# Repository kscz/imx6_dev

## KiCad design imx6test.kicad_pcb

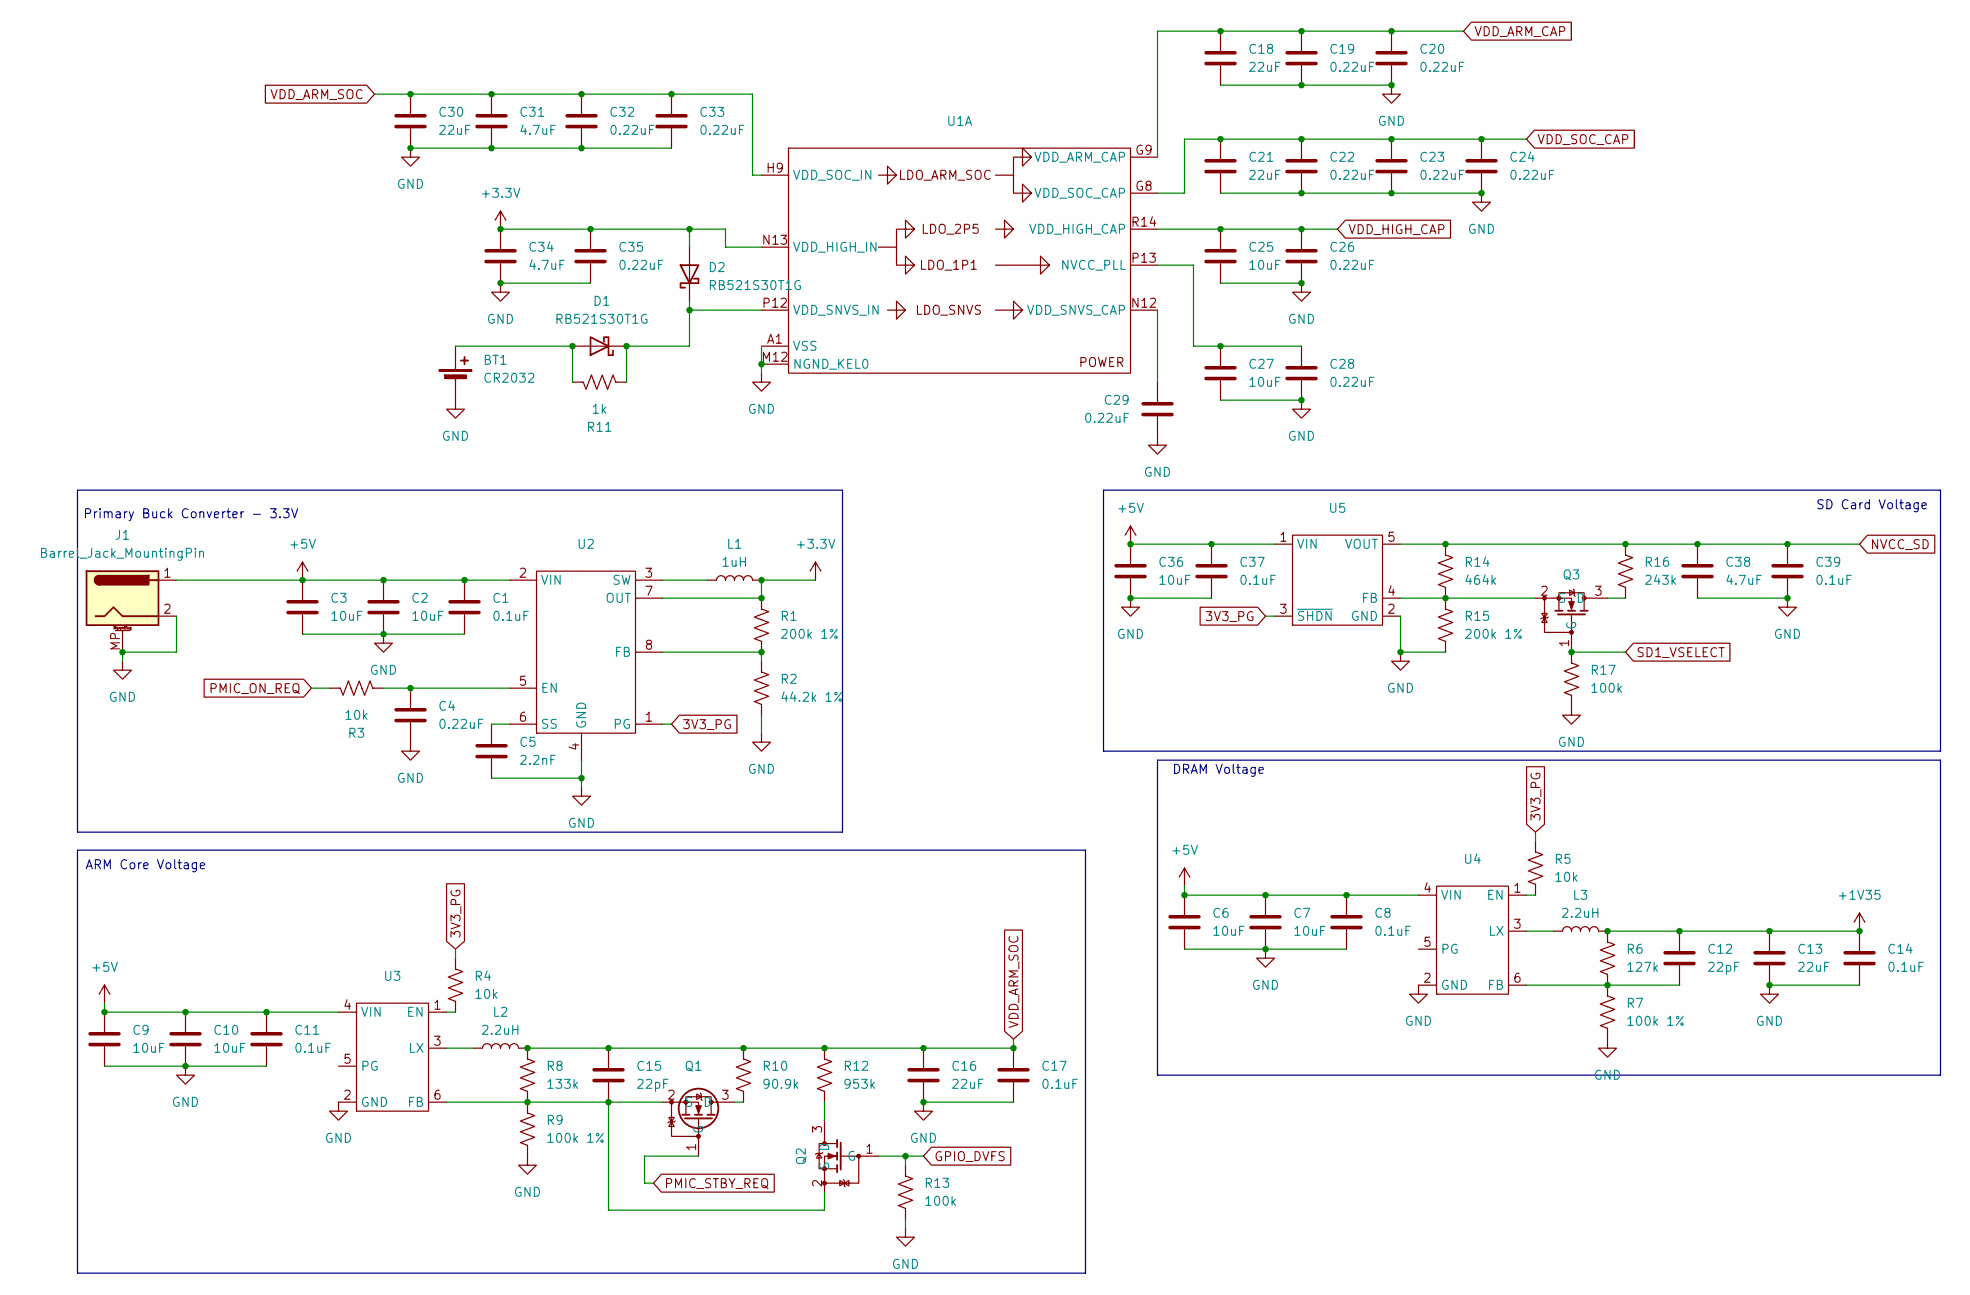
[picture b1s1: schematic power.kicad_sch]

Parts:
BT1: CR2032; BatteryHolder_Renata_SMTU2032-LF_1x2032; LCSC Part # C18212226
C1, C8, C11, C14, C17, C37, C39: 0.1uF; C_0402_1005Metric
C2, C3, C6, C7, C9, C10, C25, C27, C36: 10uF; C_0603_1608Metric
C4, C19, C20, C22, C23, C24, C26, C28, C29, C32, C33, C35: 0.22uF; C_0402_1005Metric
C5: 2.2nF; C_0402_1005Metric
C12, C15: 22pF; C_0402_1005Metric
C13, C16, C18, C21, C30: 22uF; C_0603_1608Metric
C31, C34, C38: 4.7uF; C_0402_1005Metric
D1, D2: RB521S30T1G; D_SOD-523
J1: Barrel_Jack_MountingPin; BarrelJack_CUI_PJ-063AH_Horizontal; LCSC Part # C22434582
L1: 1uH
L2, L3: 2.2uH
Q1: SC-89; LCSC Part # C509962
Q2, Q3: SOT-323_SC-70; LCSC Part # C113315
R1, R15: 200k 1%; R_0402_1005Metric
R2: 44.2k 1%; R_0402_1005Metric
R3, R4, R5: 10k; R_0402_1005Metric
R6: 127k; R_0402_1005Metric
R7, R9: 100k 1%; R_0402_1005Metric
R8: 133k; R_0402_1005Metric
R10: 90.9k; R_0402_1005Metric
R11: 1k; R_0402_1005Metric
R12: 953k; R_0402_1005Metric
R13, R17: 100k; R_0402_1005Metric
R14: 464k; R_0402_1005Metric
R16: 243k; R_0402_1005Metric
U1: MAPBGA_14x14mm_Layout17x17_P0.8mm; LCSC Part # C414042
U2: SOT-583-8; LCSC Part # C3193214
U3, U4: TSOT26; LCSC Part # C3194257
U5: SOT-23-5; LCSC Part # C620011

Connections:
3V3_PG: R4.2, R5.2, U2.1 (PG), U5.3 (~SHDN)
+1V35: C12.1, C13.1, C14.1, L3.2, R6.2; also elsewhere on the board
+3.3V: C34.1, C35.1, D2.2 (A), L1.2, R1.1, U1.N13 (VDD_HIGH_IN), U2.7 (OUT); also elsewhere on the board
+5V: C1.1, C2.1, C3.1, C6.1, C7.1, C8.1, C9.1, C10.1, C11.1, C36.1, C37.1, J1.1, U2.2 (VIN), U3.4 (VIN), U4.4 (VIN), U5.1 (VIN); also elsewhere on the board
GND: BT1.2 (-), C1.2, C2.2, C3.2, C4.2, C5.2, C6.2, C7.2, C8.2, C9.2, C10.2, C11.2, C13.2, C14.2, C16.2, C17.2, C18.2, C19.2, C20.2, C21.2, C22.2, C23.2, C24.2, C25.2, C26.2, C27.2, C28.2, C29.2, C30.2, C31.2, C32.2, C33.2, C34.2, C35.2, C36.2, C37.2, C38.2, C39.2, J1.2, J1.MP (MountPin), R2.2, R7.1, R9.1, R13.1, R15.1, R17.1, U1.A1 (VSS), U1.A17 (VSS), U1.C3 (VSS), U1.C7 (VSS), U1.C11 (VSS), U1.C15 (VSS), U1.E8 (VSS), U1.E11 (VSS), U1.F6 (VSS), U1.F7 (VSS), U1.F8 (VSS), U1.F9 (VSS), U1.F10 (VSS), U1.F11 (VSS), U1.F12 (VSS), U1.G3 (VSS), U1.G5 (VSS), U1.G7 (VSS), U1.G12 (VSS), U1.G15 (VSS), U1.H7 (VSS), U1.H12 (VSS), U1.J5 (VSS), U1.J7 (VSS), U1.J12 (VSS), U1.K7 (VSS), U1.K12 (VSS), U1.L3 (VSS), U1.L7 (VSS), U1.L12 (VSS), U1.M7 (VSS), U1.M8 (VSS), U1.M9 (VSS), U1.M10 (VSS), U1.M11 (VSS), U1.M12 (NGND_KEL0), U1.N3 (VSS), U1.N5 (VSS), U1.R3 (VSS), U1.R5 (VSS), U1.R7 (VSS), U1.R11 (VSS), U1.R16 (VSS), U1.R17 (VSS), U1.T14 (VSS), U1.U1 (VSS), U1.U14 (VSS), U1.U17 (VSS), U2.4 (GND), U3.2 (GND), U4.2 (GND), U5.2 (GND); also elsewhere on the board
GPIO_DVFS: Q2.1 (G), R13.2; also elsewhere on the board
NVCC_SD: C38.1, C39.1, R14.2, R16.2, U5.5 (VOUT); also elsewhere on the board
unnamed: BT1.1 (+), D1.2 (A), R11.1
unnamed: D1.1 (K), D2.1 (K), R11.2, U1.P12 (VDD_SNVS_IN)
unnamed: Q1.3 (D), R10.1
unnamed: C15.2, Q1.2 (S), Q2.2 (S), R8.1, R9.2, U3.6 (FB)
unnamed: Q2.3 (D), R12.1
unnamed: Q3.3 (D), R16.1
unnamed: Q3.2 (S), R14.1, R15.2, U5.4 (FB)
unnamed: C27.1, C28.1, U1.P13 (NVCC_PLL)
unnamed: C29.1, U1.N12 (VDD_SNVS_CAP)
unnamed: C4.1, R3.2, U2.5 (EN)
unnamed: R1.2, R2.1, U2.8 (FB)
unnamed: C5.1, U2.6 (SS)
unnamed: L1.1, U2.3 (SW)
unnamed: R4.1, U3.1 (EN)
unnamed: L2.1, U3.3 (LX)
unnamed: R5.1, U4.1 (EN)
unnamed: C12.2, R6.1, R7.2, U4.6 (FB)
unnamed: L3.1, U4.3 (LX)
PMIC_ON_REQ: R3.1; also elsewhere on the board
PMIC_STBY_REQ: Q1.1 (G); also elsewhere on the board
SD1_VSELECT: Q3.1 (G), R17.2; also elsewhere on the board
VDD_ARM_CAP: C18.1, C19.1, C20.1, U1.G9 (VDD_ARM_CAP), U1.G10 (VDD_ARM_CAP), U1.G11 (VDD_ARM_CAP), U1.H11 (VDD_ARM_CAP)
VDD_ARM_SOC: C15.1, C16.1, C17.1, C30.1, C31.1, C32.1, C33.1, L2.2, R8.2, R10.2, R12.2, U1.H9 (VDD_SOC_IN), U1.H10 (VDD_SOC_IN), U1.J9 (VDD_SOC_IN), U1.J10 (VDD_SOC_IN), U1.K9 (VDD_SOC_IN), U1.K10 (VDD_SOC_IN)
VDD_HIGH_CAP: C25.1, C26.1, U1.R14 (VDD_HIGH_CAP), U1.R15 (VDD_HIGH_CAP); also elsewhere on the board
VDD_SOC_CAP: C21.1, C22.1, C23.1, C24.1, U1.G8 (VDD_SOC_CAP), U1.H8 (VDD_SOC_CAP), U1.J8 (VDD_SOC_CAP), U1.J11 (VDD_SOC_CAP), U1.K8 (VDD_SOC_CAP), U1.K11 (VDD_SOC_CAP), U1.L8 (VDD_SOC_CAP), U1.L9 (VDD_SOC_CAP), U1.L10 (VDD_SOC_CAP), U1.L11 (VDD_SOC_CAP)

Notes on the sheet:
Primary Buck Converter - 3.3V
SD Card Voltage
ARM Core Voltage
DRAM Voltage

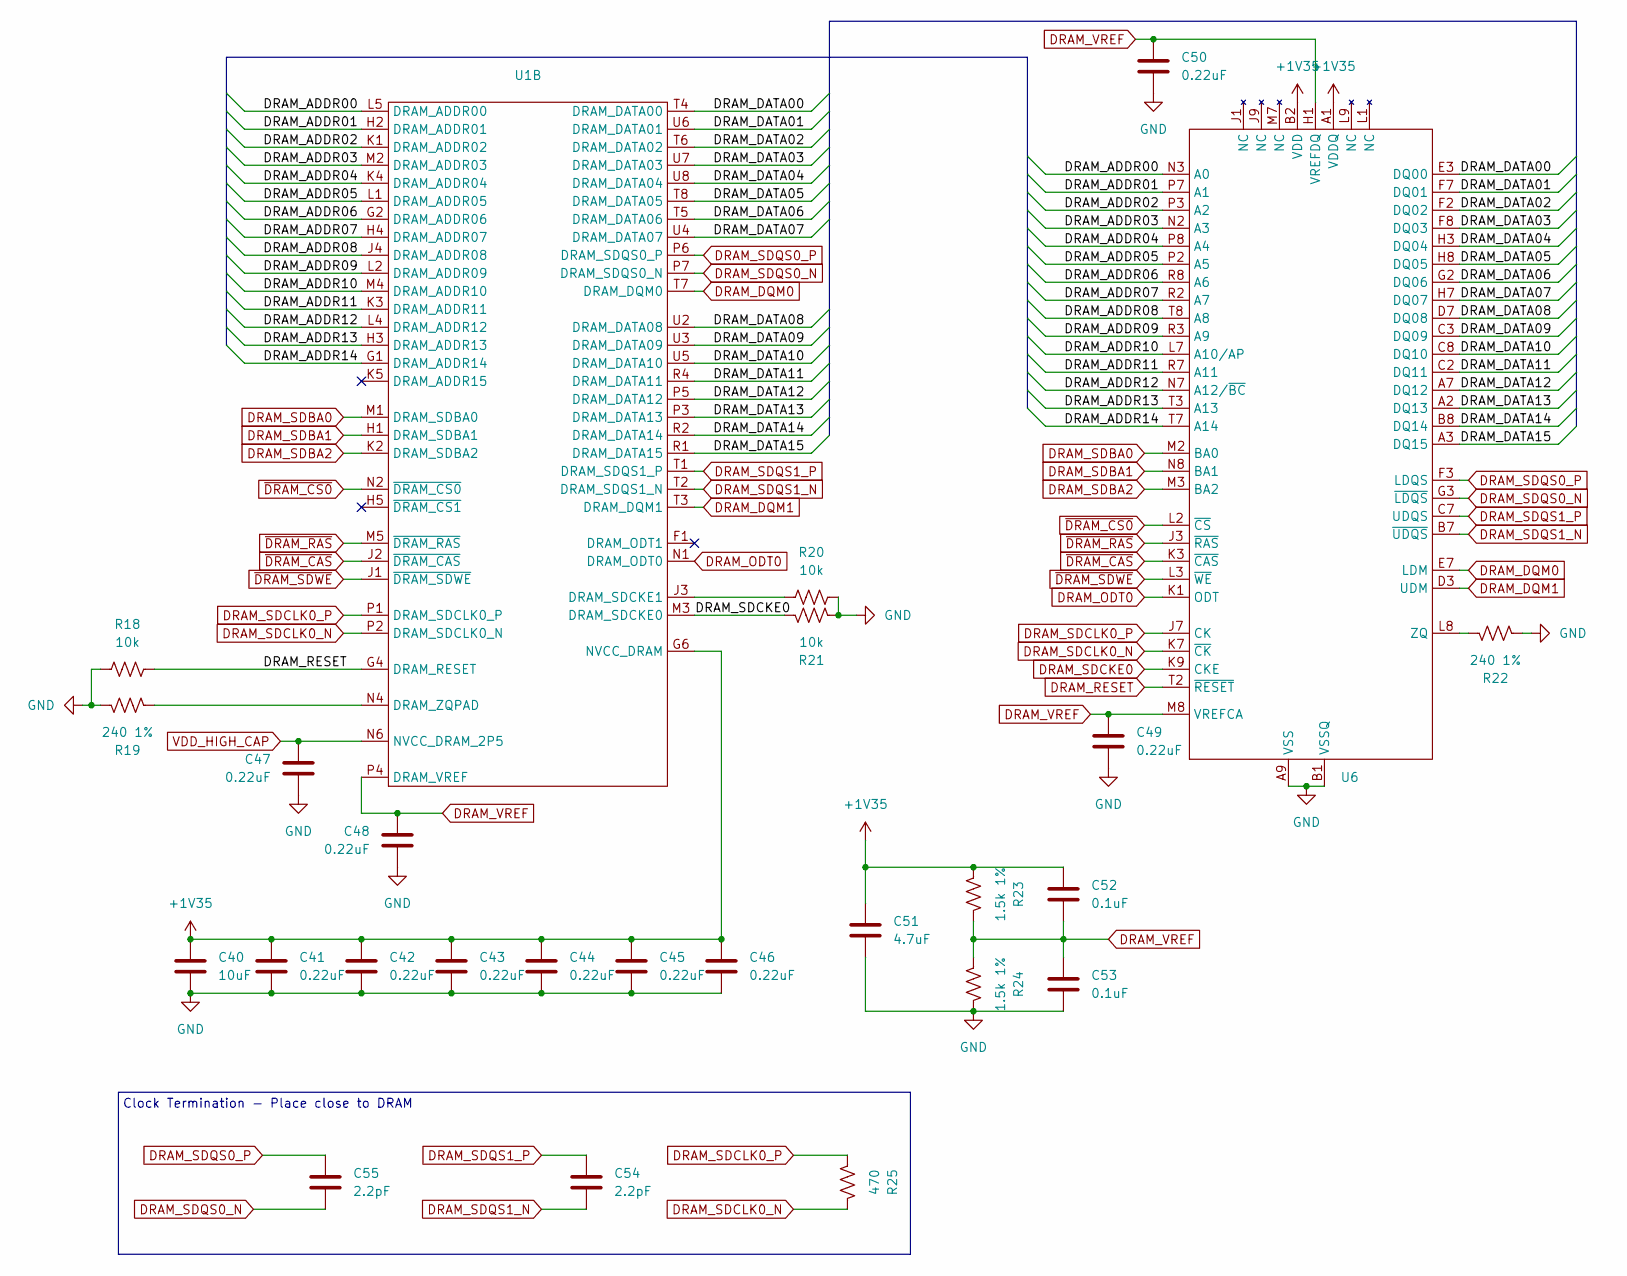
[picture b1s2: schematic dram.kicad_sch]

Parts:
C40: 10uF; C_0603_1608Metric
C41, C42, C43, C44, C45, C46, C47, C48, C49, C50: 0.22uF; C_0402_1005Metric
C51: 4.7uF; C_0402_1005Metric
C52, C53: 0.1uF; C_0402_1005Metric
C54, C55: 2.2pF; C_0402_1005Metric
R18, R20, R21: 10k; R_0402_1005Metric
R19, R22: 240 1%; R_0402_1005Metric
R23, R24: 1.5k 1%; R_0402_1005Metric
R25: 470; R_0402_1005Metric
U1: MAPBGA_14x14mm_Layout17x17_P0.8mm; LCSC Part # C414042
U6: TFBGA-96; LCSC Part # C253882

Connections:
+1V35: C40.1, C41.1, C42.1, C43.1, C44.1, C45.1, C46.1, C51.1, C52.1, R23.2, U1.G6 (NVCC_DRAM), U1.H6 (NVCC_DRAM), U1.J6 (NVCC_DRAM), U1.K6 (NVCC_DRAM), U1.L6 (NVCC_DRAM), U1.M6 (NVCC_DRAM), U6.A1 (VDDQ), U6.A8 (VDDQ), U6.B2 (VDD), U6.C1 (VDDQ), U6.C9 (VDDQ), U6.D2 (VDDQ), U6.D9 (VDD), U6.E9 (VDDQ), U6.F1 (VDDQ), U6.G7 (VDD), U6.H2 (VDDQ), U6.H9 (VDDQ), U6.K2 (VDD), U6.K8 (VDD), U6.N1 (VDD), U6.N9 (VDD), U6.R1 (VDD), U6.R9 (VDD); also elsewhere on the board
/DRAM/DRAM_ADDR00: U1.L5 (DRAM_ADDR00), U6.N3 (A0)
/DRAM/DRAM_ADDR01: U1.H2 (DRAM_ADDR01), U6.P7 (A1)
/DRAM/DRAM_ADDR02: U1.K1 (DRAM_ADDR02), U6.P3 (A2)
/DRAM/DRAM_ADDR03: U1.M2 (DRAM_ADDR03), U6.N2 (A3)
/DRAM/DRAM_ADDR04: U1.K4 (DRAM_ADDR04), U6.P8 (A4)
/DRAM/DRAM_ADDR05: U1.L1 (DRAM_ADDR05), U6.P2 (A5)
/DRAM/DRAM_ADDR06: U1.G2 (DRAM_ADDR06), U6.R8 (A6)
/DRAM/DRAM_ADDR07: U1.H4 (DRAM_ADDR07), U6.R2 (A7)
/DRAM/DRAM_ADDR08: U1.J4 (DRAM_ADDR08), U6.T8 (A8)
/DRAM/DRAM_ADDR09: U1.L2 (DRAM_ADDR09), U6.R3 (A9)
/DRAM/DRAM_ADDR10: U1.M4 (DRAM_ADDR10), U6.L7 (A10/AP)
/DRAM/DRAM_ADDR11: U1.K3 (DRAM_ADDR11), U6.R7 (A11)
/DRAM/DRAM_ADDR12: U1.L4 (DRAM_ADDR12), U6.N7 (A12/~BC)
/DRAM/DRAM_ADDR13: U1.H3 (DRAM_ADDR13), U6.T3 (A13)
/DRAM/DRAM_ADDR14: U1.G1 (DRAM_ADDR14), U6.T7 (A14)
/DRAM/DRAM_DATA00: U1.T4 (DRAM_DATA00), U6.E3 (DQ00)
/DRAM/DRAM_DATA01: U1.U6 (DRAM_DATA01), U6.F7 (DQ01)
/DRAM/DRAM_DATA02: U1.T6 (DRAM_DATA02), U6.F2 (DQ02)
/DRAM/DRAM_DATA03: U1.U7 (DRAM_DATA03), U6.F8 (DQ03)
/DRAM/DRAM_DATA04: U1.U8 (DRAM_DATA04), U6.H3 (DQ04)
/DRAM/DRAM_DATA05: U1.T8 (DRAM_DATA05), U6.H8 (DQ05)
/DRAM/DRAM_DATA06: U1.T5 (DRAM_DATA06), U6.G2 (DQ06)
/DRAM/DRAM_DATA07: U1.U4 (DRAM_DATA07), U6.H7 (DQ07)
/DRAM/DRAM_DATA08: U1.U2 (DRAM_DATA08), U6.D7 (DQ08)
/DRAM/DRAM_DATA09: U1.U3 (DRAM_DATA09), U6.C3 (DQ09)
/DRAM/DRAM_DATA10: U1.U5 (DRAM_DATA10), U6.C8 (DQ10)
/DRAM/DRAM_DATA11: U1.R4 (DRAM_DATA11), U6.C2 (DQ11)
/DRAM/DRAM_DATA12: U1.P5 (DRAM_DATA12), U6.A7 (DQ12)
/DRAM/DRAM_DATA13: U1.P3 (DRAM_DATA13), U6.A2 (DQ13)
/DRAM/DRAM_DATA14: U1.R2 (DRAM_DATA14), U6.B8 (DQ14)
/DRAM/DRAM_DATA15: U1.R1 (DRAM_DATA15), U6.A3 (DQ15)
DRAM_DQM0: U1.T7 (DRAM_DQM0), U6.E7 (LDM)
DRAM_DQM1: U1.T3 (DRAM_DQM1), U6.D3 (UDM)
DRAM_ODT0: U1.N1 (DRAM_ODT0), U6.K1 (ODT)
DRAM_RESET: R18.2, U1.G4 (DRAM_RESET), U6.T2 (~RESET)
DRAM_SDBA0: U1.M1 (DRAM_SDBA0), U6.M2 (BA0)
DRAM_SDBA1: U1.H1 (DRAM_SDBA1), U6.N8 (BA1)
DRAM_SDBA2: U1.K2 (DRAM_SDBA2), U6.M3 (BA2)
DRAM_SDCKE0: R21.1, U1.M3 (DRAM_SDCKE0), U6.K9 (CKE)
DRAM_SDCLK0_N: R25.1, U1.P2 (DRAM_SDCLK0_N), U6.K7 (~CK)
DRAM_SDCLK0_P: R25.2, U1.P1 (DRAM_SDCLK0_P), U6.J7 (CK)
DRAM_SDQS0_N: C55.2, U1.P7 (DRAM_SDQS0_N), U6.G3 (~LDQS)
DRAM_SDQS0_P: C55.1, U1.P6 (DRAM_SDQS0_P), U6.F3 (LDQS)
DRAM_SDQS1_N: C54.2, U1.T2 (DRAM_SDQS1_N), U6.B7 (~UDQS)
DRAM_SDQS1_P: C54.1, U1.T1 (DRAM_SDQS1_P), U6.C7 (UDQS)
DRAM_VREF: C48.1, C49.1, C50.1, C52.2, C53.1, R23.1, R24.2, U1.P4 (DRAM_VREF), U6.H1 (VREFDQ), U6.M8 (VREFCA)
GND: C40.2, C41.2, C42.2, C43.2, C44.2, C45.2, C46.2, C47.2, C48.2, C49.2, C50.2, C51.2, C53.2, R18.1, R19.1, R20.2, R21.2, R22.2, R24.1, U6.A9 (VSS), U6.B1 (VSSQ), U6.B3 (VSS), U6.B9 (VSSQ), U6.D1 (VSSQ), U6.D8 (VSSQ), U6.E1 (VSS), U6.E2 (VSSQ), U6.E8 (VSSQ), U6.F9 (VSSQ), U6.G1 (VSSQ), U6.G8 (VSS), U6.G9 (VSSQ), U6.J2 (VSS), U6.J8 (VSS), U6.M1 (VSS), U6.M9 (VSS), U6.P1 (VSS), U6.P9 (VSS), U6.T1 (VSS), U6.T9 (VSS); also elsewhere on the board
unnamed: R20.1, U1.J3 (DRAM_SDCKE1)
unnamed: R19.2, U1.N4 (DRAM_ZQPAD)
unnamed: R22.1, U6.L8 (ZQ)
VDD_HIGH_CAP: C47.1, U1.N6 (NVCC_DRAM_2P5); also elsewhere on the board
~DRAM_CAS: U1.J2 (~DRAM_CAS), U6.K3 (~CAS)
~DRAM_CS0: U1.N2 (~DRAM_CS0), U6.L2 (~CS)
~DRAM_RAS: U1.M5 (~DRAM_RAS), U6.J3 (~RAS)
~DRAM_SDWE: U1.J1 (~DRAM_SDWE), U6.L3 (~WE)

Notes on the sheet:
Clock Termination - Place close to DRAM

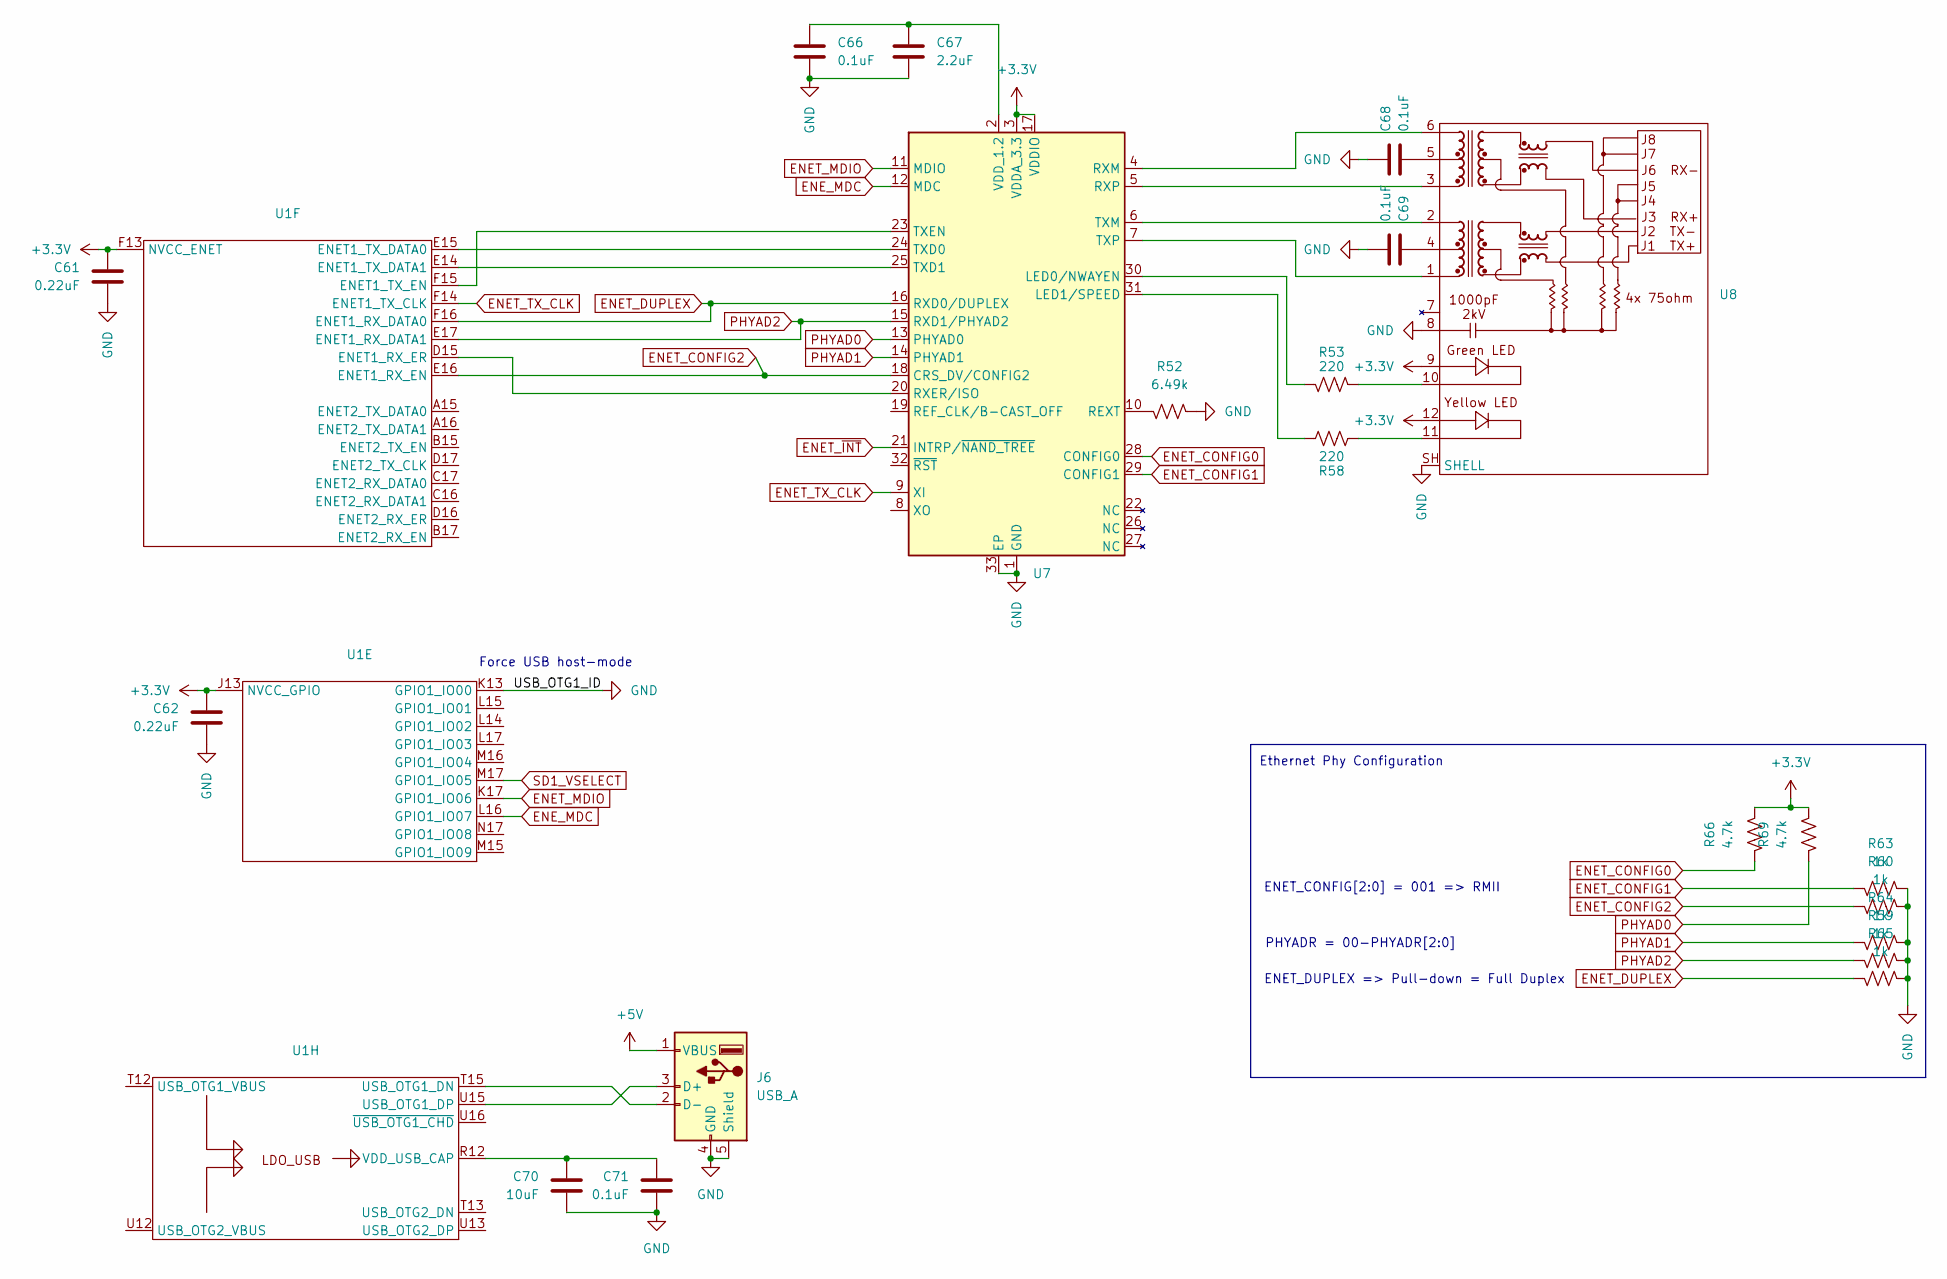
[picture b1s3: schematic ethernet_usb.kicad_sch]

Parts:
C61, C62: 0.22uF; C_0402_1005Metric
C66, C68, C69, C71: 0.1uF; C_0402_1005Metric
C67: 2.2uF; C_0402_1005Metric
C70: 10uF; C_0603_1608Metric
J6: USB_A; USB_A_Molex_67643_Horizontal; LCSC Part # C293351
R52: 6.49k; R_0402_1005Metric
R53, R58: 220; R_0402_1005Metric
R59, R60, R63, R64, R65: 1k; R_0402_1005Metric
R66, R69: 4.7k; R_0402_1005Metric
U1: MAPBGA_14x14mm_Layout17x17_P0.8mm; LCSC Part # C414042
U7: QFN-32-1EP_5x5mm_P0.5mm_EP3.1x3.1mm; LCSC Part # C100018
U8: HR9011105A; LCSC Part # C12074

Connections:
+3.3V: C61.1, C62.1, R66.1, R69.1, U1.F13 (NVCC_ENET), U1.J13 (NVCC_GPIO), U7.3 (VDDA_3.3), U7.17 (VDDIO), U8.9, U8.12; also elsewhere on the board
+5V: J6.1 (VBUS); also elsewhere on the board
ENET_CONFIG0: R66.2, U7.28 (CONFIG0)
ENET_CONFIG1: R63.2, U7.29 (CONFIG1)
ENET_CONFIG2: R60.2, U1.E16 (ENET1_RX_EN), U7.18 (CRS_DV/CONFIG2)
ENET_DUPLEX: R65.2, U1.F16 (ENET1_RX_DATA0), U7.16 (RXD0/DUPLEX)
ENET_MDIO: U1.K17 (GPIO1_IO06), U7.11 (MDIO)
ENET_TX_CLK: U1.F14 (ENET1_TX_CLK), U7.9 (XI)
ENET_~INT: U7.21 (INTRP/~NAND_TREE); also elsewhere on the board
ENE_MDC: U1.L16 (GPIO1_IO07), U7.12 (MDC)
GND: C61.2, C62.2, C66.2, C67.2, C68.1, C69.2, C70.2, C71.2, J6.4 (GND), J6.5 (Shield), R52.1, R59.1, R60.1, R63.1, R64.1, R65.1, U1.K13 (GPIO1_IO00), U7.1 (GND), U7.33 (EP), U8.8, U8.SH (SHELL); also elsewhere on the board
unnamed: C68.2, U8.5
unnamed: C69.1, U8.4
unnamed: J6.3 (D+), U1.U15 (USB_OTG1_DP)
unnamed: J6.2 (D-), U1.T15 (USB_OTG1_DN)
unnamed: R53.1, U8.10
unnamed: R58.1, U8.11
unnamed: U1.D15 (ENET1_RX_ER), U7.20 (RXER/ISO)
unnamed: U1.E15 (ENET1_TX_DATA0), U7.24 (TXD0)
unnamed: U1.E14 (ENET1_TX_DATA1), U7.25 (TXD1)
unnamed: U1.F15 (ENET1_TX_EN), U7.23 (TXEN)
unnamed: C70.1, C71.1, U1.R12 (VDD_USB_CAP)
unnamed: R53.2, U7.30 (LED0/NWAYEN)
unnamed: R58.2, U7.31 (LED1/SPEED)
unnamed: R52.2, U7.10 (REXT)
unnamed: U7.4 (RXM), U8.6
unnamed: U7.5 (RXP), U8.3
unnamed: U7.6 (TXM), U8.2
unnamed: U7.7 (TXP), U8.1
unnamed: C66.1, C67.1, U7.2 (VDD_1.2)
PHYAD0: R69.2, U7.13 (PHYAD0)
PHYAD1: R64.2, U7.14 (PHYAD1)
PHYAD2: R59.2, U1.E17 (ENET1_RX_DATA1), U7.15 (RXD1/PHYAD2)
SD1_VSELECT: U1.M17 (GPIO1_IO05); also elsewhere on the board

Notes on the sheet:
PHYADR = 00-PHYADR[2:0]
ENET_CONFIG[2:0] = 001 => RMII
Force USB host-mode
Ethernet Phy Configuration
ENET_DUPLEX => Pull-down = Full Duplex

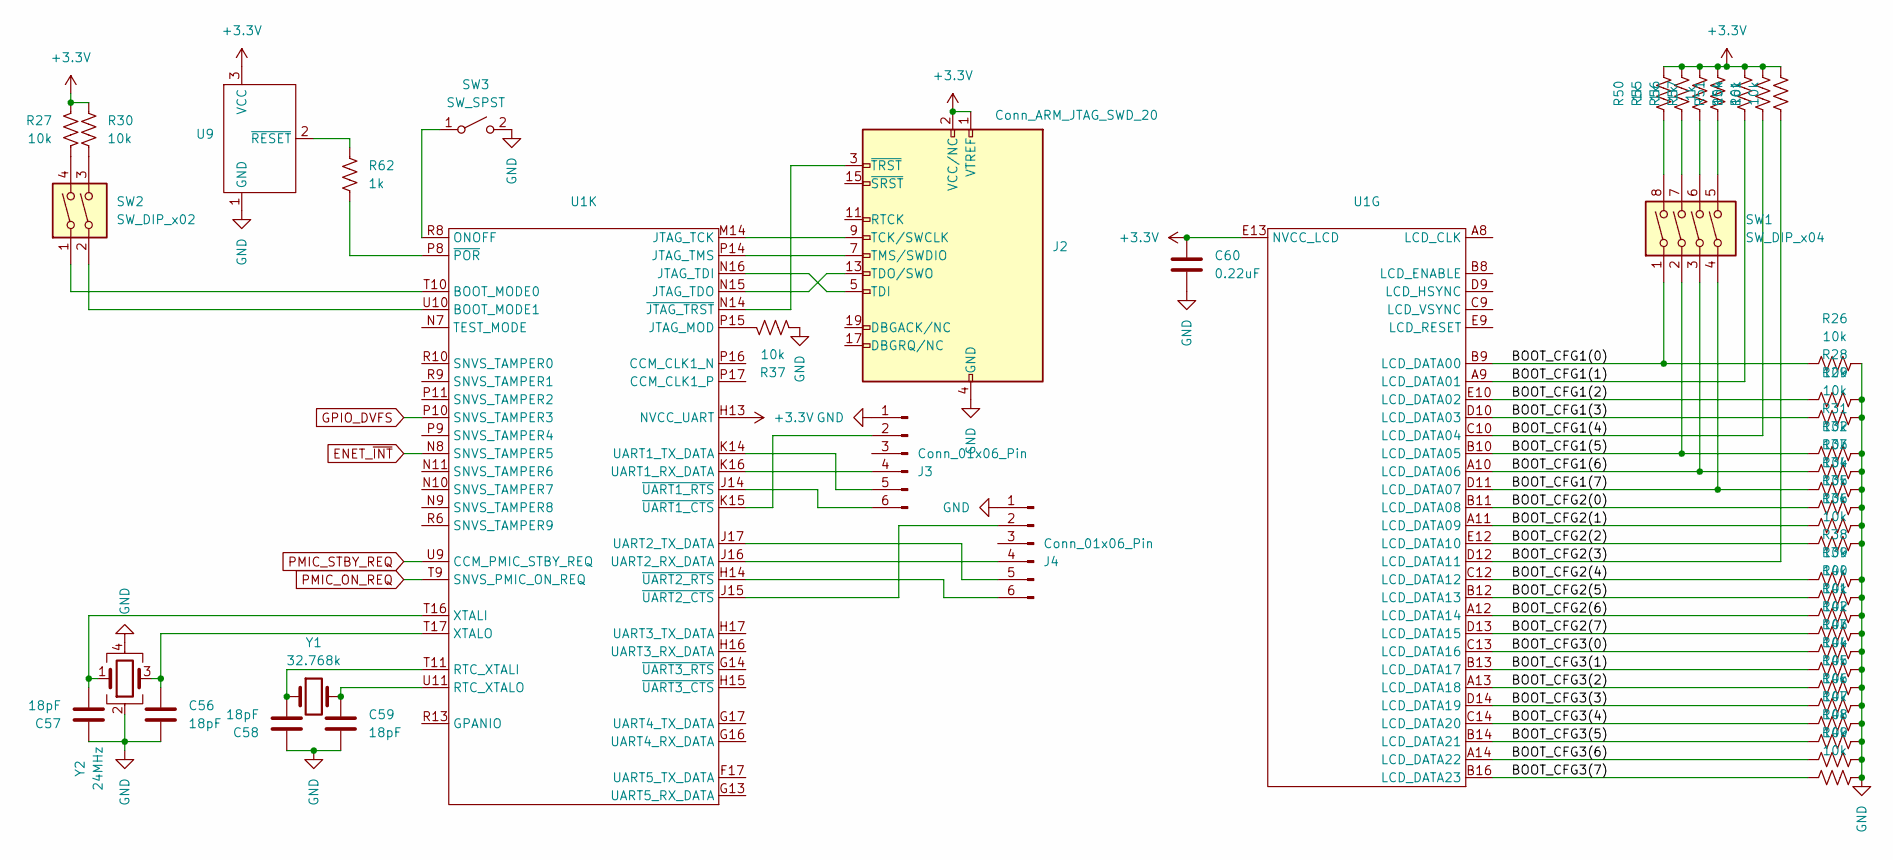
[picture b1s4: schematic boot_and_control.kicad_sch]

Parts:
C56, C57, C58, C59: 18pF; C_0402_1005Metric
C60: 0.22uF; C_0402_1005Metric
J2: Conn_ARM_JTAG_SWD_20; PinHeader_2x10_P2.54mm_Vertical
J3, J4: Conn_01x06_Pin; PinHeader_1x06_P2.54mm_Vertical
R26, R27, R28, R29, R30, R31, R32, R33, R34, R35, R36, R37, R38, R39, R40, R41, R42, R43, R44, R45, R46, R47, R48, R49, R51, R54, R61: 10k; R_0402_1005Metric
R50, R55, R56, R57, R62: 1k; R_0402_1005Metric
SW1: SW_DIP_x04; SW_DIP_SPSTx04_Slide_Omron_A6S-410x_W8.9mm_P2.54mm
SW2: SW_DIP_x02
SW3: SW_SPST; SW_SPST_Omron_B3FS-100xP
U1: MAPBGA_14x14mm_Layout17x17_P0.8mm; LCSC Part # C414042
U9: SOT-23-3; LCSC Part # C620009
Y1: 32.768k; Crystal_SMD_3215-2Pin_3.2x1.5mm; LCSC Part # C5366538
Y2: 24MHz; Crystal_SMD_SeikoEpson_TSX3225-4Pin_3.2x2.5mm; LCSC Part # C5807375

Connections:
+3.3V: C60.1, J2.1 (VTREF), J2.2 (VCC/NC), R27.2, R30.2, R50.2, R51.2, R54.2, R55.2, R56.2, R57.2, R61.2, U1.E13 (NVCC_LCD), U1.H13 (NVCC_UART), U9.3 (VCC); also elsewhere on the board
/Boot and Control/BOOT_CFG1(0): R26.1, SW1.1, U1.B9 (LCD_DATA00)
/Boot and Control/BOOT_CFG1(1): R51.1, U1.A9 (LCD_DATA01)
/Boot and Control/BOOT_CFG1(2): R28.1, U1.E10 (LCD_DATA02)
/Boot and Control/BOOT_CFG1(3): R29.1, U1.D10 (LCD_DATA03)
/Boot and Control/BOOT_CFG1(4): R54.1, U1.C10 (LCD_DATA04)
/Boot and Control/BOOT_CFG1(5): R31.1, SW1.2, U1.B10 (LCD_DATA05)
/Boot and Control/BOOT_CFG1(6): R32.1, SW1.3, U1.A10 (LCD_DATA06)
/Boot and Control/BOOT_CFG1(7): R33.1, SW1.4, U1.D11 (LCD_DATA07)
/Boot and Control/BOOT_CFG2(0): R34.1, U1.B11 (LCD_DATA08)
/Boot and Control/BOOT_CFG2(1): R35.1, U1.A11 (LCD_DATA09)
/Boot and Control/BOOT_CFG2(2): R36.1, U1.E12 (LCD_DATA10)
/Boot and Control/BOOT_CFG2(3): R61.1, U1.D12 (LCD_DATA11)
/Boot and Control/BOOT_CFG2(4): R38.1, U1.C12 (LCD_DATA12)
/Boot and Control/BOOT_CFG2(5): R39.1, U1.B12 (LCD_DATA13)
/Boot and Control/BOOT_CFG2(6): R40.1, U1.A12 (LCD_DATA14)
/Boot and Control/BOOT_CFG2(7): R41.1, U1.D13 (LCD_DATA15)
/Boot and Control/BOOT_CFG3(0): R42.1, U1.C13 (LCD_DATA16)
/Boot and Control/BOOT_CFG3(1): R43.1, U1.B13 (LCD_DATA17)
/Boot and Control/BOOT_CFG3(2): R44.1, U1.A13 (LCD_DATA18)
/Boot and Control/BOOT_CFG3(3): R45.1, U1.D14 (LCD_DATA19)
/Boot and Control/BOOT_CFG3(4): R46.1, U1.C14 (LCD_DATA20)
/Boot and Control/BOOT_CFG3(5): R47.1, U1.B14 (LCD_DATA21)
/Boot and Control/BOOT_CFG3(6): R48.1, U1.A14 (LCD_DATA22)
/Boot and Control/BOOT_CFG3(7): R49.1, U1.B16 (LCD_DATA23)
ENET_~INT: U1.N8 (SNVS_TAMPER5); also elsewhere on the board
GND: C56.2, C57.1, C58.1, C59.2, C60.2, J2.4 (GND), J2.6 (GND), J2.8 (GND), J2.10 (GND), J2.12 (GND), J2.14 (GND), J2.16 (GND), J2.18 (GND), J2.20 (GND), J3.1, J4.1, R26.2, R28.2, R29.2, R31.2, R32.2, R33.2, R34.2, R35.2, R36.2, R37.2, R38.2, R39.2, R40.2, R41.2, R42.2, R43.2, R44.2, R45.2, R46.2, R47.2, R48.2, R49.2, SW3.2 (B), U9.1 (GND), Y2.2, Y2.4; also elsewhere on the board
GPIO_DVFS: U1.P10 (SNVS_TAMPER3); also elsewhere on the board
unnamed: J2.9 (TCK/SWCLK), U1.M14 (JTAG_TCK)
unnamed: J2.5 (TDI), U1.N16 (JTAG_TDI)
unnamed: J2.13 (TDO/SWO), U1.N15 (JTAG_TDO)
unnamed: J2.7 (TMS/SWDIO), U1.P14 (JTAG_TMS)
unnamed: J2.3 (~TRST), U1.N14 (~JTAG_TRST)
unnamed: J3.2, U1.K15 (~UART1_CTS)
unnamed: J3.4, U1.K16 (UART1_RX_DATA)
unnamed: J3.5, U1.K14 (UART1_TX_DATA)
unnamed: J3.6, U1.J14 (~UART1_RTS)
unnamed: J4.2, U1.J15 (~UART2_CTS)
unnamed: J4.4, U1.J16 (UART2_RX_DATA)
unnamed: J4.5, U1.J17 (UART2_TX_DATA)
unnamed: J4.6, U1.H14 (~UART2_RTS)
unnamed: R27.1, SW2.4
unnamed: R30.1, SW2.3
unnamed: R50.1, SW1.8
unnamed: R55.1, SW1.7
unnamed: R56.1, SW1.6
unnamed: R57.1, SW1.5
unnamed: SW3.1 (A), U1.R8 (ONOFF)
unnamed: SW2.1, U1.T10 (BOOT_MODE0)
unnamed: SW2.2, U1.U10 (BOOT_MODE1)
unnamed: R37.1, U1.P15 (JTAG_MOD)
unnamed: C58.2, U1.T11 (RTC_XTALI), Y1.1
unnamed: C59.1, U1.U11 (RTC_XTALO), Y1.2
unnamed: C57.2, U1.T16 (XTALI), Y2.1
unnamed: C56.1, U1.T17 (XTALO), Y2.3
unnamed: R62.1, U1.P8 (~POR)
unnamed: R62.2, U9.2 (~RESET)
PMIC_ON_REQ: U1.T9 (SNVS_PMIC_ON_REQ); also elsewhere on the board
PMIC_STBY_REQ: U1.U9 (CCM_PMIC_STBY_REQ); also elsewhere on the board

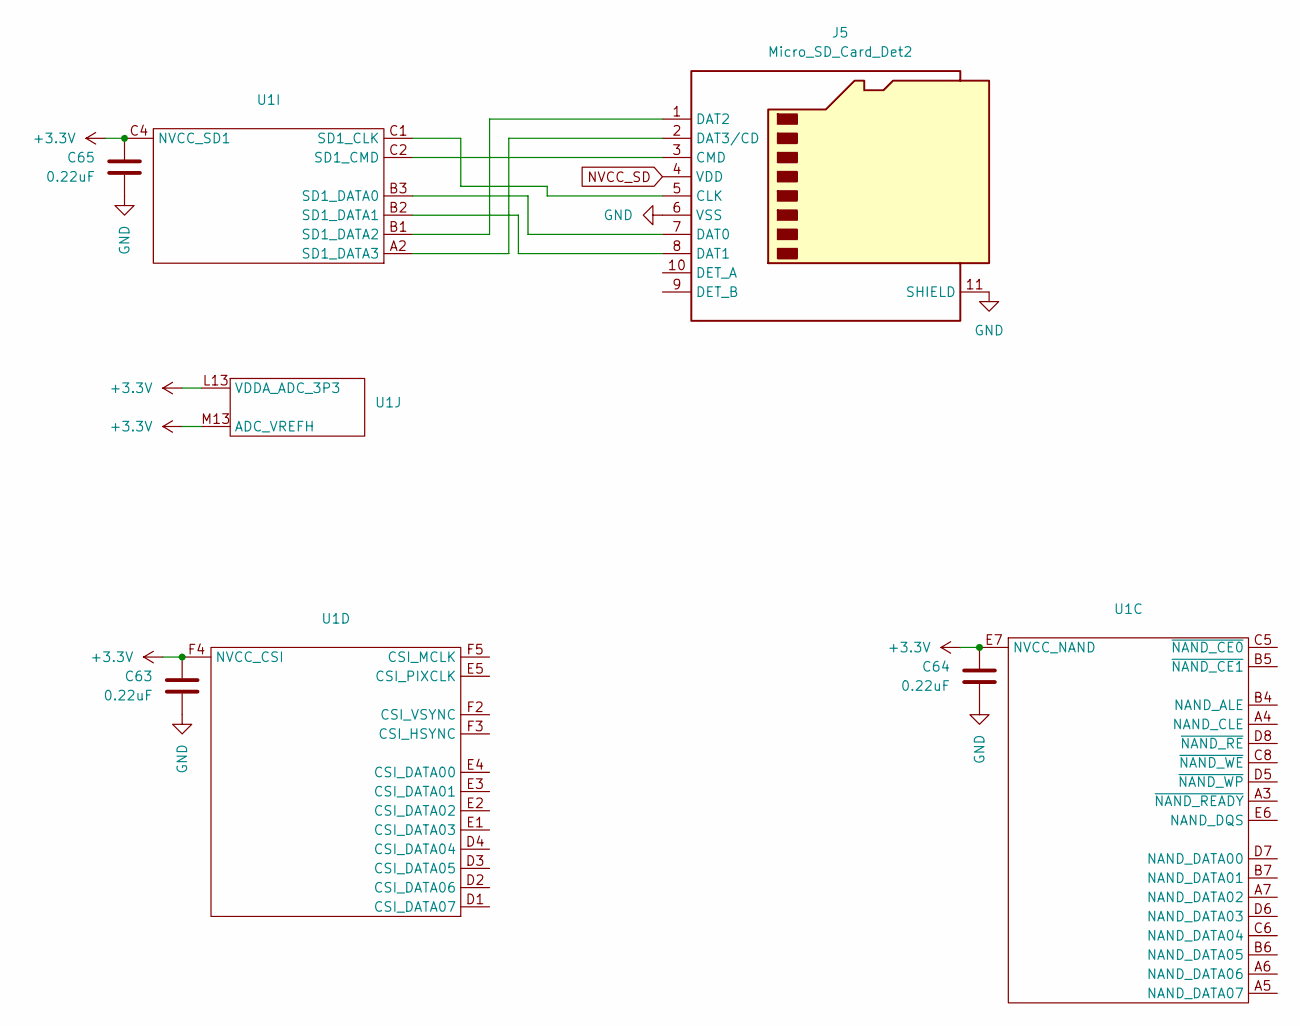
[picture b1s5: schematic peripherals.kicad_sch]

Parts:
C63, C64, C65: 0.22uF; C_0402_1005Metric
J5: Micro_SD_Card_Det2; microSD_HC_Hirose_DM3AT-SF-PEJM5; LCSC Part # C114218
U1: MAPBGA_14x14mm_Layout17x17_P0.8mm; LCSC Part # C414042

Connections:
+3.3V: C63.1, C64.1, C65.1, U1.C4 (NVCC_SD1), U1.E7 (NVCC_NAND), U1.F4 (NVCC_CSI), U1.L13 (VDDA_ADC_3P3), U1.M13 (ADC_VREFH); also elsewhere on the board
GND: C63.2, C64.2, C65.2, J5.6 (VSS), J5.11 (SHIELD); also elsewhere on the board
NVCC_SD: J5.4 (VDD); also elsewhere on the board
unnamed: J5.5 (CLK), U1.C1 (SD1_CLK)
unnamed: J5.3 (CMD), U1.C2 (SD1_CMD)
unnamed: J5.7 (DAT0), U1.B3 (SD1_DATA0)
unnamed: J5.8 (DAT1), U1.B2 (SD1_DATA1)
unnamed: J5.1 (DAT2), U1.B1 (SD1_DATA2)
unnamed: J5.2 (DAT3/CD), U1.A2 (SD1_DATA3)

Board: 4 copper layers, 163 parts (2 on the bottom side), 167 nets, no tracks yet.

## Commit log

2024-10-15 Initial commit - design largely complete
2024-10-20 Add in on-off switch, power-on reset controller
2024-10-21 Add in LCSC part numbers for major parts, assign packages
2024-10-22 Add in datasheet references
2026-02-13 Small update
